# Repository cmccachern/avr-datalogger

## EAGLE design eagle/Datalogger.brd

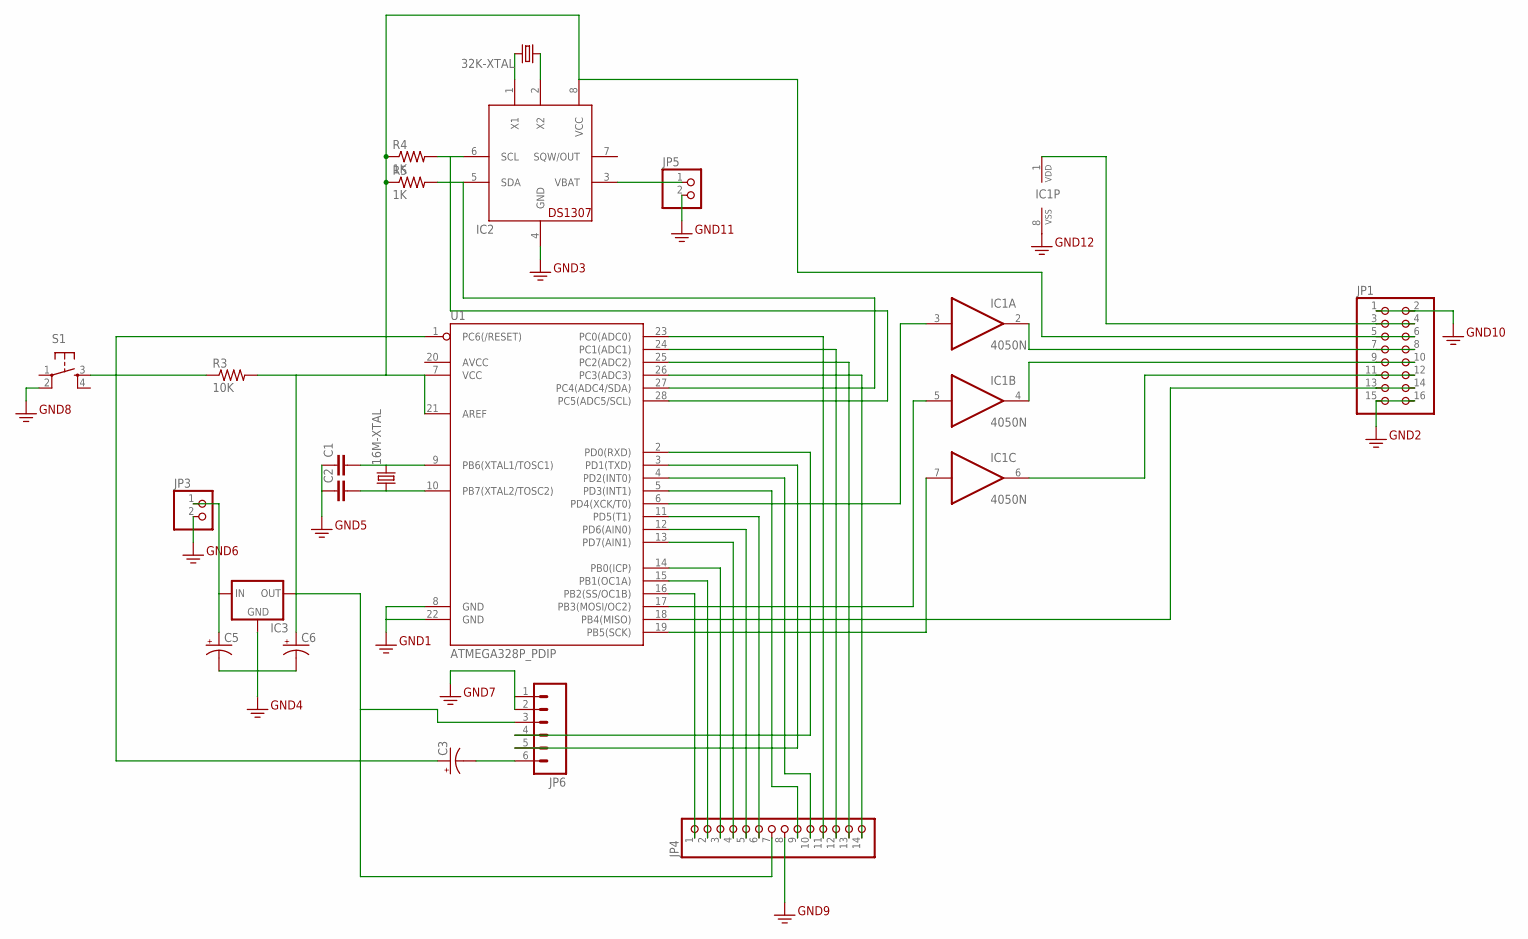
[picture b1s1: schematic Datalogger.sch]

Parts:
16M-XTAL: CRYSTALHC49US; HC49US
32K-XTAL: CRYSTALTC26H_EZ; TC26HEZ
C1, C2: CAPKIT; CAP-PTH-SMALL-KIT
C3, C5, C6: CAP_POLPTH1; CPOL-RADIAL-100UF-25V
IC1: 4050N; DIL16
IC2: DS1307; DIL08
IC3: V_REG_78XX-TO-220; TO-220-ALT
JP1: PINHD-2X8; 2X08
JP3, JP5: PINHD-1X2; 1X02
JP4: PINHD-1X14; 1X14
JP6: M06SIP; 1X06
R3: 10K; AXIAL-0.4
R4, R5: 1K; AXIAL-0.4
S1: TAC_SWITCHPTH; TACTILE-PTH
U1: ATMEGA328P_PDIP; DIL28-3

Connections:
3.3V: C1.1, C2.1, C5.2 (-), C6.2 (-), IC1.8 (VSS), IC2.4 (GND), IC3.GND, JP1.1, JP1.2, JP1.15, JP1.16, JP3.2, JP4.8, JP5.2, JP6.1, JP6.2, S1.2, U1.8 (GND), U1.22 (GND)
unnamed: JP4.2, U1.15 (PB1(OC1A))
unnamed: 16M-XTAL.2, C1.2, U1.9 (PB6(XTAL1/TOSC1))
unnamed: 16M-XTAL.1, C2.2, U1.10 (PB7(XTAL2/TOSC2))
unnamed: IC1.2 (O), JP1.7, JP1.8
unnamed: IC1.4 (O), JP1.9, JP1.10
unnamed: IC1.6 (O), JP1.11, JP1.12
unnamed: JP1.13, JP1.14, U1.18 (PB4(MISO))
unnamed: C6.1 (+), IC2.8 (VCC), IC3.OUT, JP1.5, JP1.6, JP4.7, JP6.3, R3.P$2 (2), R4.P$1 (1), R5.P$1 (1), U1.7 (VCC), U1.21 (AREF)
unnamed: IC1.1 (VDD), JP1.3, JP1.4
unnamed: IC1.3 (I), U1.6 (PD4(XCK/T0))
unnamed: IC1.5 (I), U1.17 (PB3(MOSI/OC2))
unnamed: IC1.7 (I), U1.19 (PB5(SCK))
unnamed: 32K-XTAL.1, IC2.2 (X2)
unnamed: 32K-XTAL.2, IC2.1 (X1)
unnamed: IC2.6 (SCL), R4.P$2 (2), U1.28 (PC5(ADC5/SCL))
unnamed: C5.1 (+), IC3.IN, JP3.1
unnamed: IC2.5 (SDA), R5.P$2 (2), U1.27 (PC4(ADC4/SDA))
unnamed: JP4.11, U1.23 (PC0(ADC0))
unnamed: IC2.3 (VBAT), JP5.1
unnamed: C3.2 (-), JP6.6
unnamed: JP4.12, U1.24 (PC1(ADC1))
unnamed: JP4.13, U1.25 (PC2(ADC2))
unnamed: JP4.14, U1.26 (PC3(ADC3))
unnamed: JP6.4, U1.2 (PD0(RXD))
unnamed: JP6.5, U1.3 (PD1(TXD))
unnamed: JP4.10, U1.4 (PD2(INT0))
unnamed: JP4.9, U1.5 (PD3(INT1))
unnamed: JP4.6, U1.11 (PD5(T1))
unnamed: JP4.5, U1.12 (PD6(AIN0))
unnamed: JP4.4, U1.13 (PD7(AIN1))
unnamed: JP4.3, U1.14 (PB0(ICP))
unnamed: C3.1 (+), U1.1 (PC6(/RESET))
unnamed: JP4.1, U1.16 (PB2(SS/OC1B))
unnamed: R3.P$1 (1), S1.3

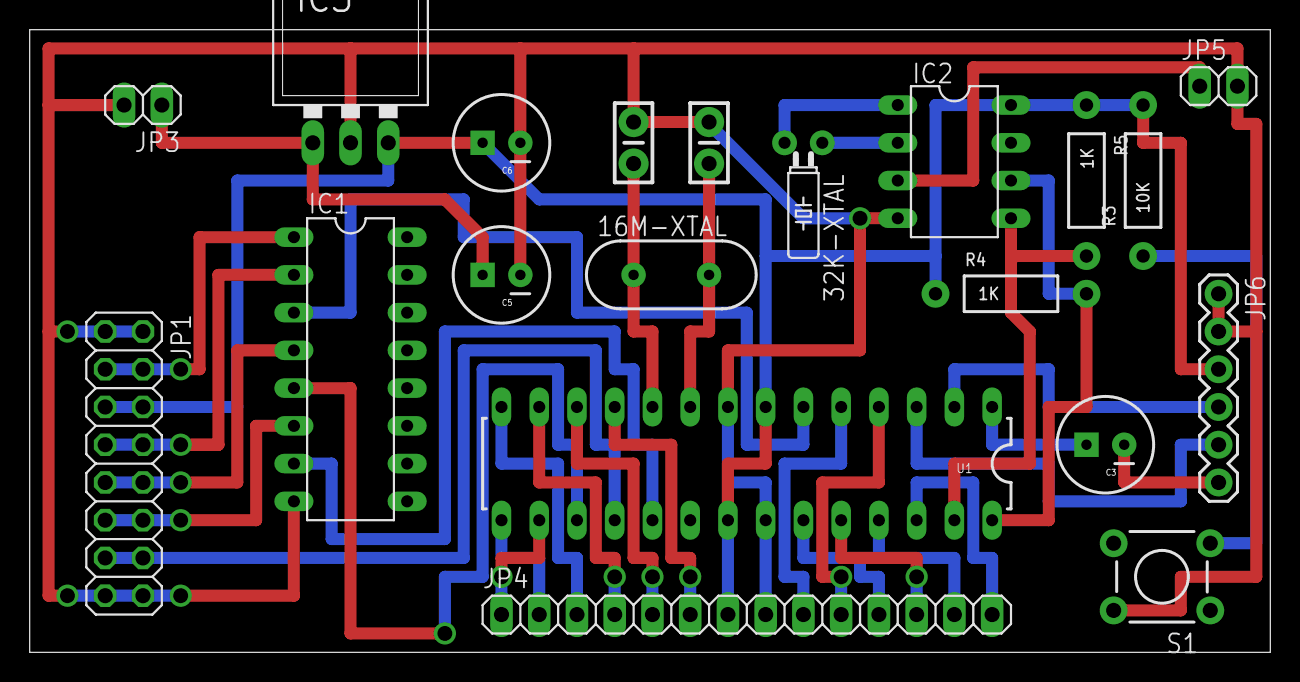
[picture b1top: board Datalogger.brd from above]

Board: 2 copper layers, 83.5 x 41.9 mm, 20 parts (0 on the bottom side), 35 nets.

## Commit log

2014-07-06 Added code

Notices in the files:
parts and their libraries:
SparkFun-DigitalIC: Licensing: CC v3.0 Share-Alike You are welcome to use this library for commercial purposes.
